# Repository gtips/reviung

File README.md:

# REVIUNG

## [REVIUNG41](https://github.com/gtips/reviung/tree/master/reviung41)  

The REVIUNG41 is 41-key column staggered keyboard.  

[Firmware](https://github.com/qmk/qmk_firmware/tree/master/keyboards/reviung/reviung41)  
[Build guide](https://reviung.com/build-guide/391/)  
  
<br>
<br>
  
## REVIUNG39 Mk-II, REVIUNG39 and REVIUNG39S  
The REVIUNG39 is 39-key column staggered keyboard.

Soldering is divided into through-hole mounting version and surface mounting (SMD) version so that the soldering difficulty can be selected.  

- REVIUNG39 Mk-II and REVIUNG39 is regular version (SMD)  
- REVIUNG39S is simple version (through-hole)  

[REVIUNG39 Mk-II ](https://github.com/gtips/reviung/tree/master/reviung39Mk-II)   

<br>

[REVIUNG39](https://github.com/gtips/reviung/tree/master/reviung39)  

<br>

[REVIUNG39 Build guide](https://reviung.com/build-guide/108/)  
[Firmware](https://github.com/qmk/qmk_firmware/tree/master/keyboards/reviung/reviung39)
  
<br>
<br>

## REVIUNG34  
The REVIUNG34 is 34-key (or33-key) column staggered keyboard.  
  
[REVIUNG34](https://github.com/gtips/reviung/tree/master/reviung34)  

<br>

[REVIUNG34 Build guide](https://reviung.com/build-guide/724/)  
[Firmware](https://github.com/qmk/qmk_firmware/tree/master/keyboards/reviung/reviung34)
  
<br>
<br>

## REVIUNG5  
The REVIUNG5 is 5-key (or 4-key + Rotary Encoder) macropad.  
  
[REVIUNG5](https://github.com/gtips/reviung/tree/master/reviung5)  

<br>

[REVIUNG5 Build guide](https://reviung.com/build-guide/)  
[Firmware](https://github.com/qmk/qmk_firmware/tree/master/keyboards/reviung/reviung5)
  
<br>
<br>
  
## REVIUNG34 SPLIT Mk-II and REVIUNG34 SPLIT  

The REVIUNG34 is 34-key split ortholinear keyboard.  
(REVIUNG34 SPLIT Mk-II is 34-key or 33-key)  
Use a LAN cable to connect the left and right keyboards.  
  
[REVIUNG34 Mk-II](https://github.com/gtips/reviung/tree/master/reviung34split_Mk-II)  

<br>
  
[REVIUNG34 SPLIT](https://github.com/gtips/reviung/tree/master/reviung34split)  

[Firmware](https://github.com/qmk/qmk_firmware/tree/master/keyboards/reviung/reviung34)  
[REVIUNG34 SPLIT Build guide](https://reviung.com/build-guide/278/)  

<br>
<br>

## [REVIUNG33](https://github.com/gtips/reviung/tree/master/reviung33)  

The REVIUNG33 is 33-key ortholinear keyboard.  

[Firmware](https://github.com/qmk/qmk_firmware/tree/master/keyboards/reviung/reviung33)  

<br>
<br>

## [REVIUNG53](https://github.com/gtips/reviung/tree/master/reviung53)  

The REVIUNG53 is 53-key keyboard.  

[Firmware](https://github.com/qmk/qmk_firmware/tree/master/keyboards/reviung/reviung53)  

<br>
<br>

## [REVIUNG61](https://github.com/gtips/reviung/tree/master/reviung61)  

Standard ANSI 60% keyboard. And compatible with MX and ALPS.  

[Firmware](https://github.com/qmk/qmk_firmware/tree/master/keyboards/reviung/reviung61)  

<br>
<br>

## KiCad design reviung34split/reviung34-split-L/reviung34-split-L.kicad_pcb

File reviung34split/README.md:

# REVIUNG34 SPLIT  

The REVIUNG34 SPLIT is 34-key split ortholinear keyboard.  
Use a LAN cable to connect the left and right keyboards.  

[Firmware](https://github.com/qmk/qmk_firmware/tree/master/keyboards/reviung/reviung34)  
[Build guide](https://reviung.com/build-guide/278/)  

#### Parts list  
1  PCB left  
1  PCB right  
1  left Top plate (PCB with switch mounting holes)  
1  right Top plate (PCB with switch mounting hole)  
2  Bottom plate (left and right common PCB)  
1  ProMicro protective plate (Comes with left top plate. Cut and use.)  
34 Diode (1N4148)  
34 PCB socket for switches  
1  Tact switch (reset button)  
2  Ethernet connector (DS1128-05-S8B8P)  
1  Stabilizer (2u)  
12 M2 spacer 7mm (metal spacer)  
24 M2 screw 5mm  
8  Rubber feet for bottom plate  
<br/>
1  ProMicro  
34 Key switch (MX compatible)  
33 Keycap (1U, MX compatible)  
1  Keycap (2U, MX compatible)  
1  MicroUSB cable  
1  Ethernet cable (Use a cable shorter than 1m)

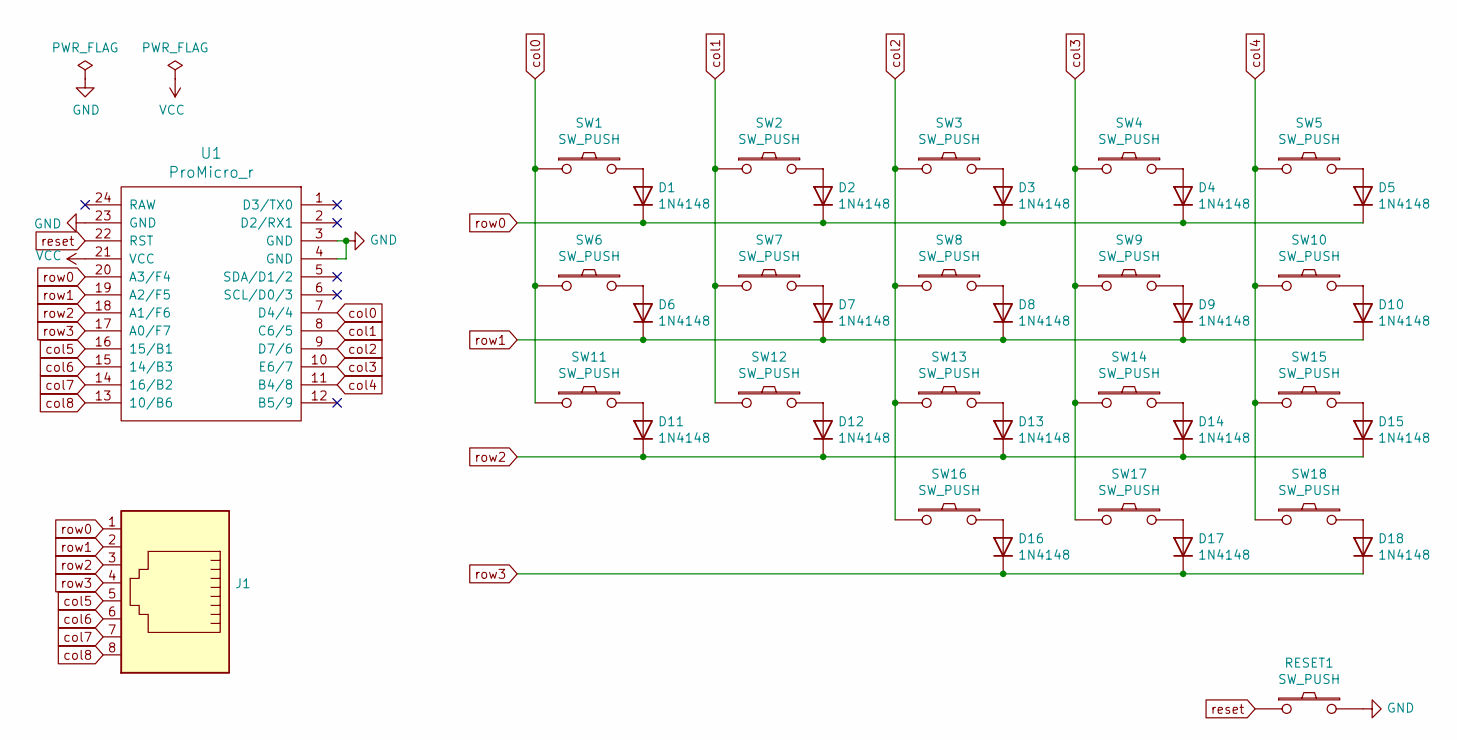
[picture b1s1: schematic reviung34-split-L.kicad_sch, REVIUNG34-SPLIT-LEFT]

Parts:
D1, D2, D3, D4, D5, D6, D7, D8, D9, D10, D11, D12, D13, D14, D15, D16, D17, D18: 1N4148; D_DO-35_SOD27_P7.62mm_Horizontal
J1: (no value)
RESET1: SW_PUSH; ResetSW_1side
SW1, SW2, SW3, SW4, SW5, SW6, SW7, SW8, SW9, SW10, SW11, SW12, SW13, SW14, SW15, SW16, SW17, SW18: SW_PUSH; MXOnly-1U-Hotswap
U1: ProMicro_r; ProMicro

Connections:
GND: RESET1.2, U1.3 (GND), U1.4 (GND), U1.23 (GND)
unnamed: D1.2 (A), SW1.2
unnamed: D2.2 (A), SW2.2
unnamed: D3.2 (A), SW3.2
unnamed: D4.2 (A), SW4.2
unnamed: D5.2 (A), SW5.2
unnamed: D6.2 (A), SW6.2
unnamed: D7.2 (A), SW7.2
unnamed: D8.2 (A), SW8.2
unnamed: D9.2 (A), SW9.2
unnamed: D10.2 (A), SW10.2
unnamed: D11.2 (A), SW11.2
unnamed: D12.2 (A), SW12.2
unnamed: D13.2 (A), SW13.2
unnamed: D14.2 (A), SW14.2
unnamed: D15.2 (A), SW15.2
unnamed: D16.2 (A), SW16.2
unnamed: D17.2 (A), SW17.2
unnamed: D18.2 (A), SW18.2
VCC: U1.21 (VCC)
col0: SW1.1, SW6.1, SW11.1, U1.7 (D4/4)
col1: SW2.1, SW7.1, SW12.1, U1.8 (C6/5)
col2: SW3.1, SW8.1, SW13.1, SW16.1, U1.9 (D7/6)
col3: SW4.1, SW9.1, SW14.1, SW17.1, U1.10 (E6/7)
col4: SW5.1, SW10.1, SW15.1, SW18.1, U1.11 (B4/8)
col5: J1.5, U1.16 (15/B1)
col6: J1.6, U1.15 (14/B3)
col7: J1.7, U1.14 (16/B2)
col8: J1.8, U1.13 (10/B6)
reset: RESET1.1, U1.22 (RST)
row0: D1.1 (K), D2.1 (K), D3.1 (K), D4.1 (K), D5.1 (K), J1.1, U1.20 (A3/F4)
row1: D6.1 (K), D7.1 (K), D8.1 (K), D9.1 (K), D10.1 (K), J1.2, U1.19 (A2/F5)
row2: D11.1 (K), D12.1 (K), D13.1 (K), D14.1 (K), D15.1 (K), J1.3, U1.18 (A1/F6)
row3: D16.1 (K), D17.1 (K), D18.1 (K), J1.4, U1.17 (A0/F7)

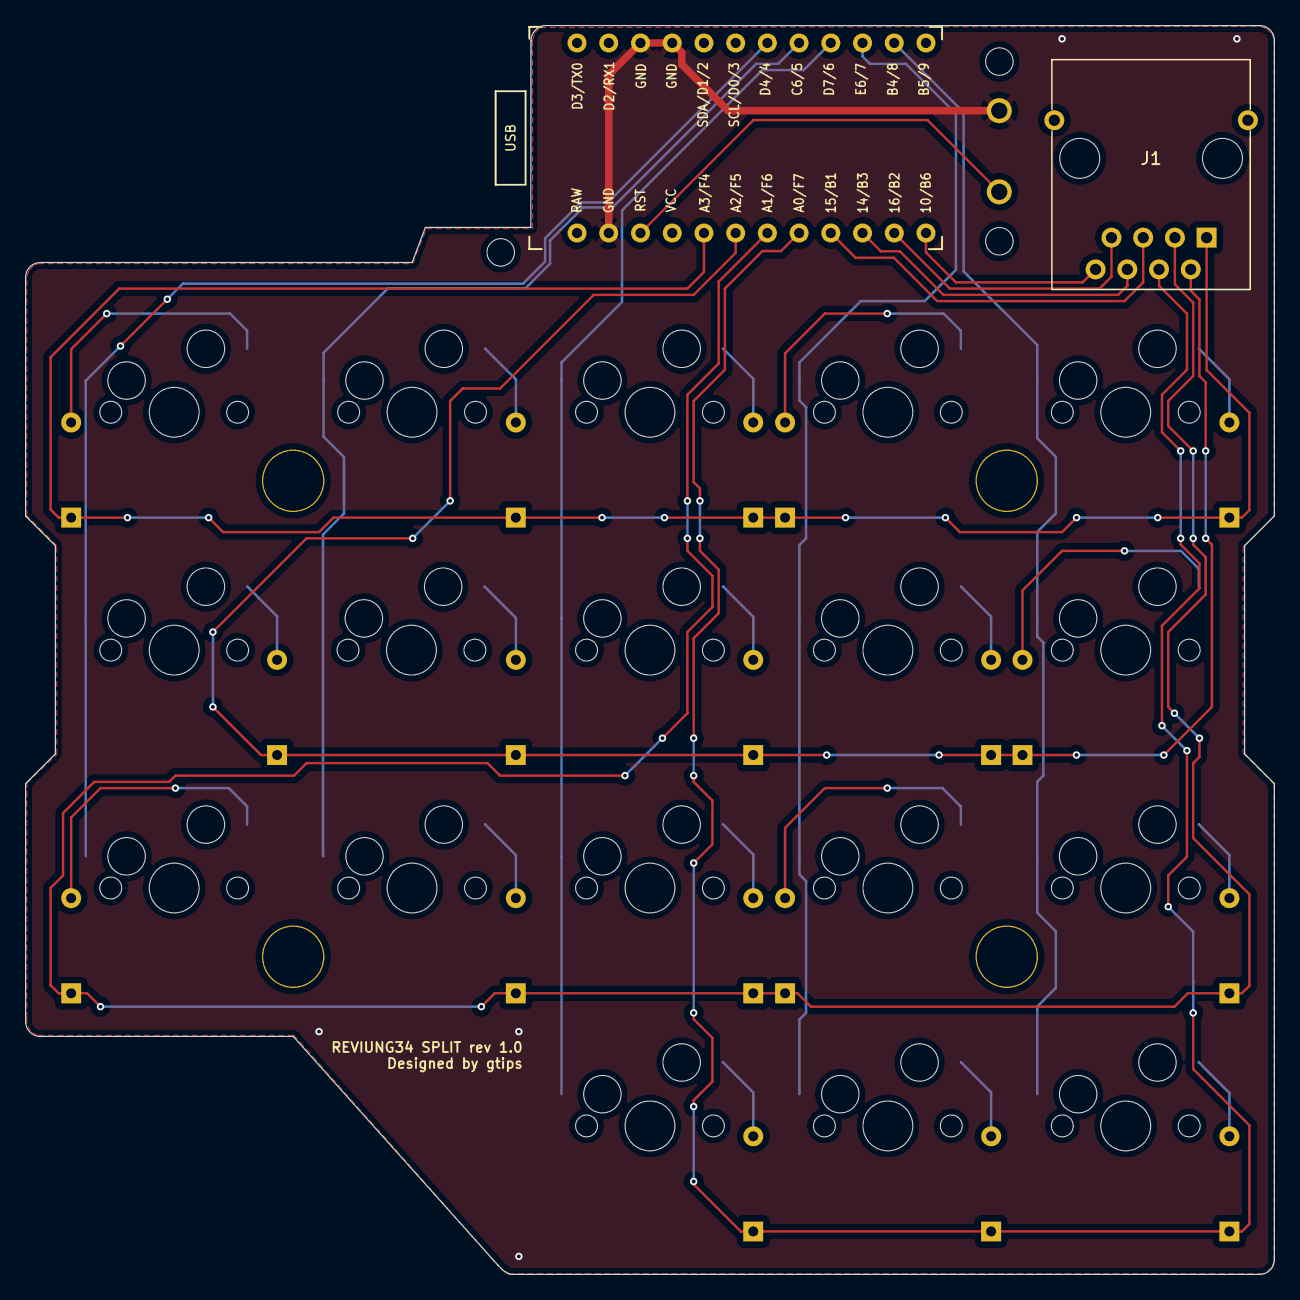
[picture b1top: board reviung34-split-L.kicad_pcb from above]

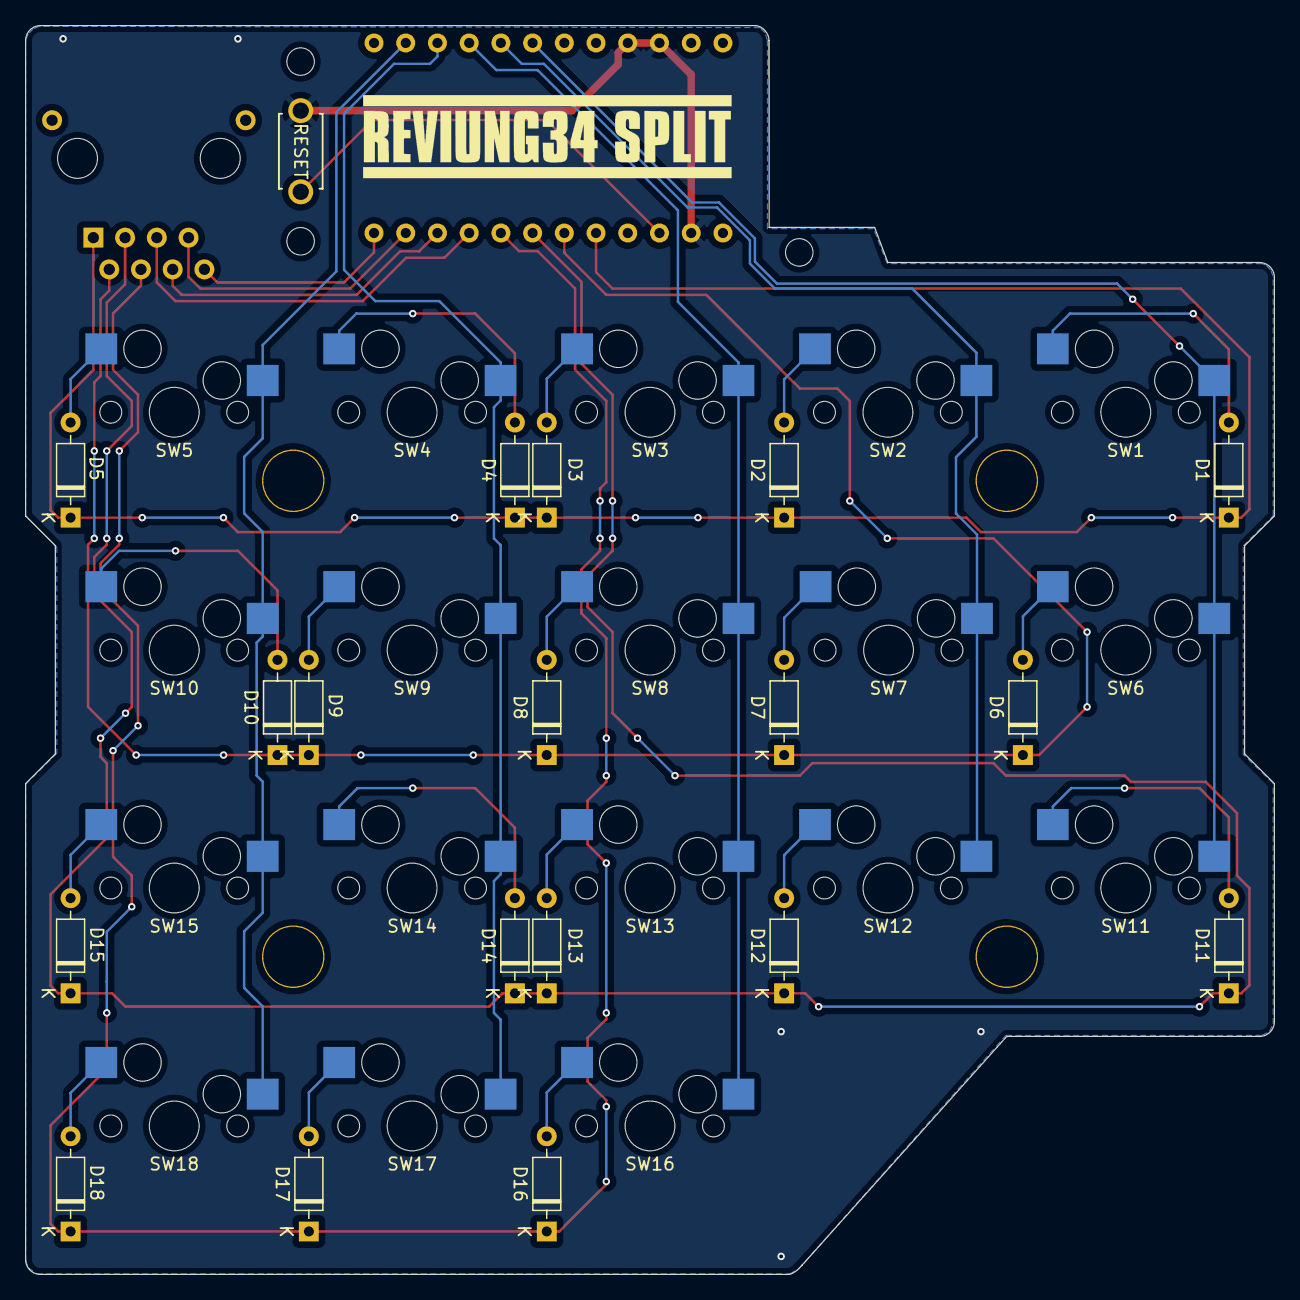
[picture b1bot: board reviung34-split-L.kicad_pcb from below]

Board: 2 copper layers, 100.0 x 100.0 mm, 46 parts (19 on the bottom side), 33 nets.

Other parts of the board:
H1: H1; HOLE
H2: H2; HOLE
H3: H3; HOLE
H4: H4; HOLE
H5, H6, H7: MountingHole_2.2mm_M2

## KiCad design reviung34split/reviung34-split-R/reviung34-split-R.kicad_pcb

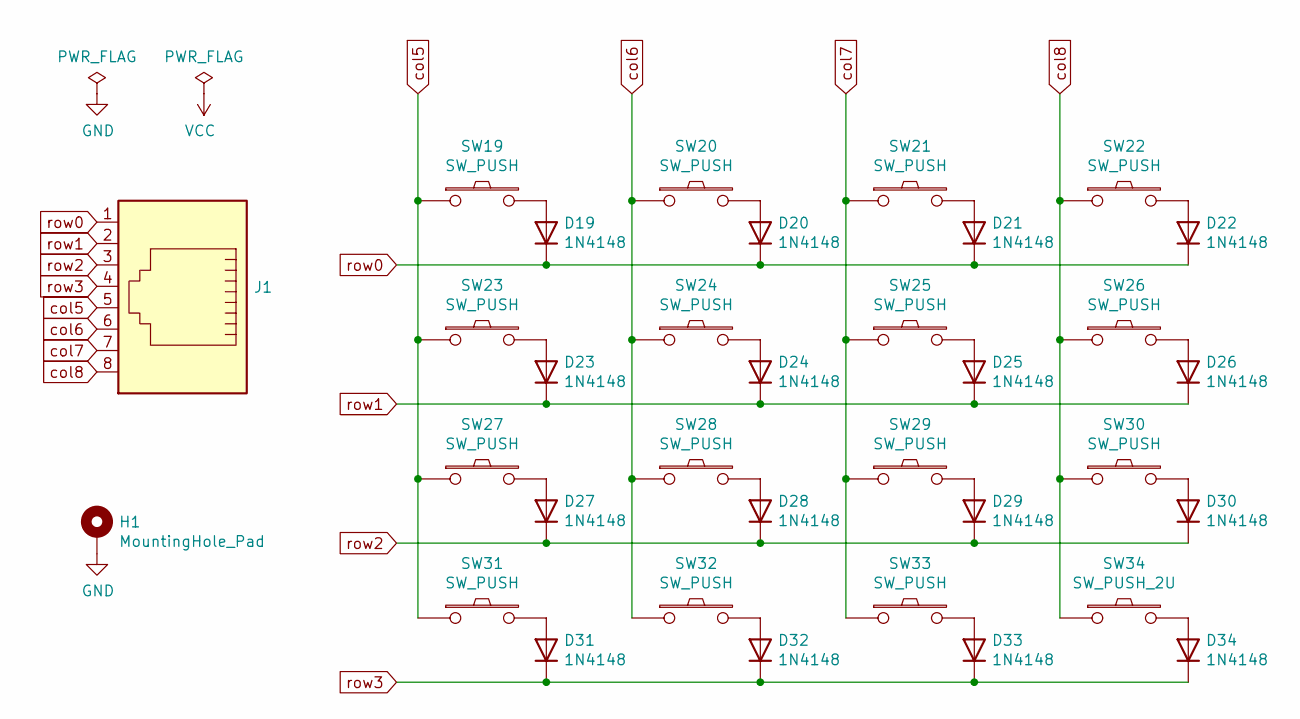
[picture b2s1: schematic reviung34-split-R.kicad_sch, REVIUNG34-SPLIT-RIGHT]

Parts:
D19, D20, D21, D22, D23, D24, D25, D26, D27, D28, D29, D30, D31, D32, D33, D34: 1N4148; D_DO-35_SOD27_P7.62mm_Horizontal
H1: MountingHole_Pad; MountingHole_4.3mm_M4_ISO14580_Pad
J1: (no value)
SW19, SW20, SW21, SW22, SW23, SW24, SW25, SW26, SW27, SW28, SW29, SW30, SW31, SW32, SW33: SW_PUSH; MXOnly-1U-Hotswap
SW34: SW_PUSH_2U; MXOnly-2U-Hotswap-ReversedStabilizers

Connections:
GND: H1.1, J1.SH
unnamed: D19.2 (A), SW19.2
unnamed: D20.2 (A), SW20.2
unnamed: D21.2 (A), SW21.2
unnamed: D22.2 (A), SW22.2
unnamed: D23.2 (A), SW23.2
unnamed: D24.2 (A), SW24.2
unnamed: D25.2 (A), SW25.2
unnamed: D26.2 (A), SW26.2
unnamed: D27.2 (A), SW27.2
unnamed: D28.2 (A), SW28.2
unnamed: D29.2 (A), SW29.2
unnamed: D30.2 (A), SW30.2
unnamed: D31.2 (A), SW31.2
unnamed: D32.2 (A), SW32.2
unnamed: D33.2 (A), SW33.2
unnamed: D34.2 (A), SW34.2
col5: J1.5, SW19.1, SW23.1, SW27.1, SW31.1
col6: J1.6, SW20.1, SW24.1, SW28.1, SW32.1
col7: J1.7, SW21.1, SW25.1, SW29.1, SW33.1
col8: J1.8, SW22.1, SW26.1, SW30.1, SW34.1
row0: D19.1 (K), D20.1 (K), D21.1 (K), D22.1 (K), J1.1
row1: D23.1 (K), D24.1 (K), D25.1 (K), D26.1 (K), J1.2
row2: D27.1 (K), D28.1 (K), D29.1 (K), D30.1 (K), J1.3
row3: D31.1 (K), D32.1 (K), D33.1 (K), D34.1 (K), J1.4

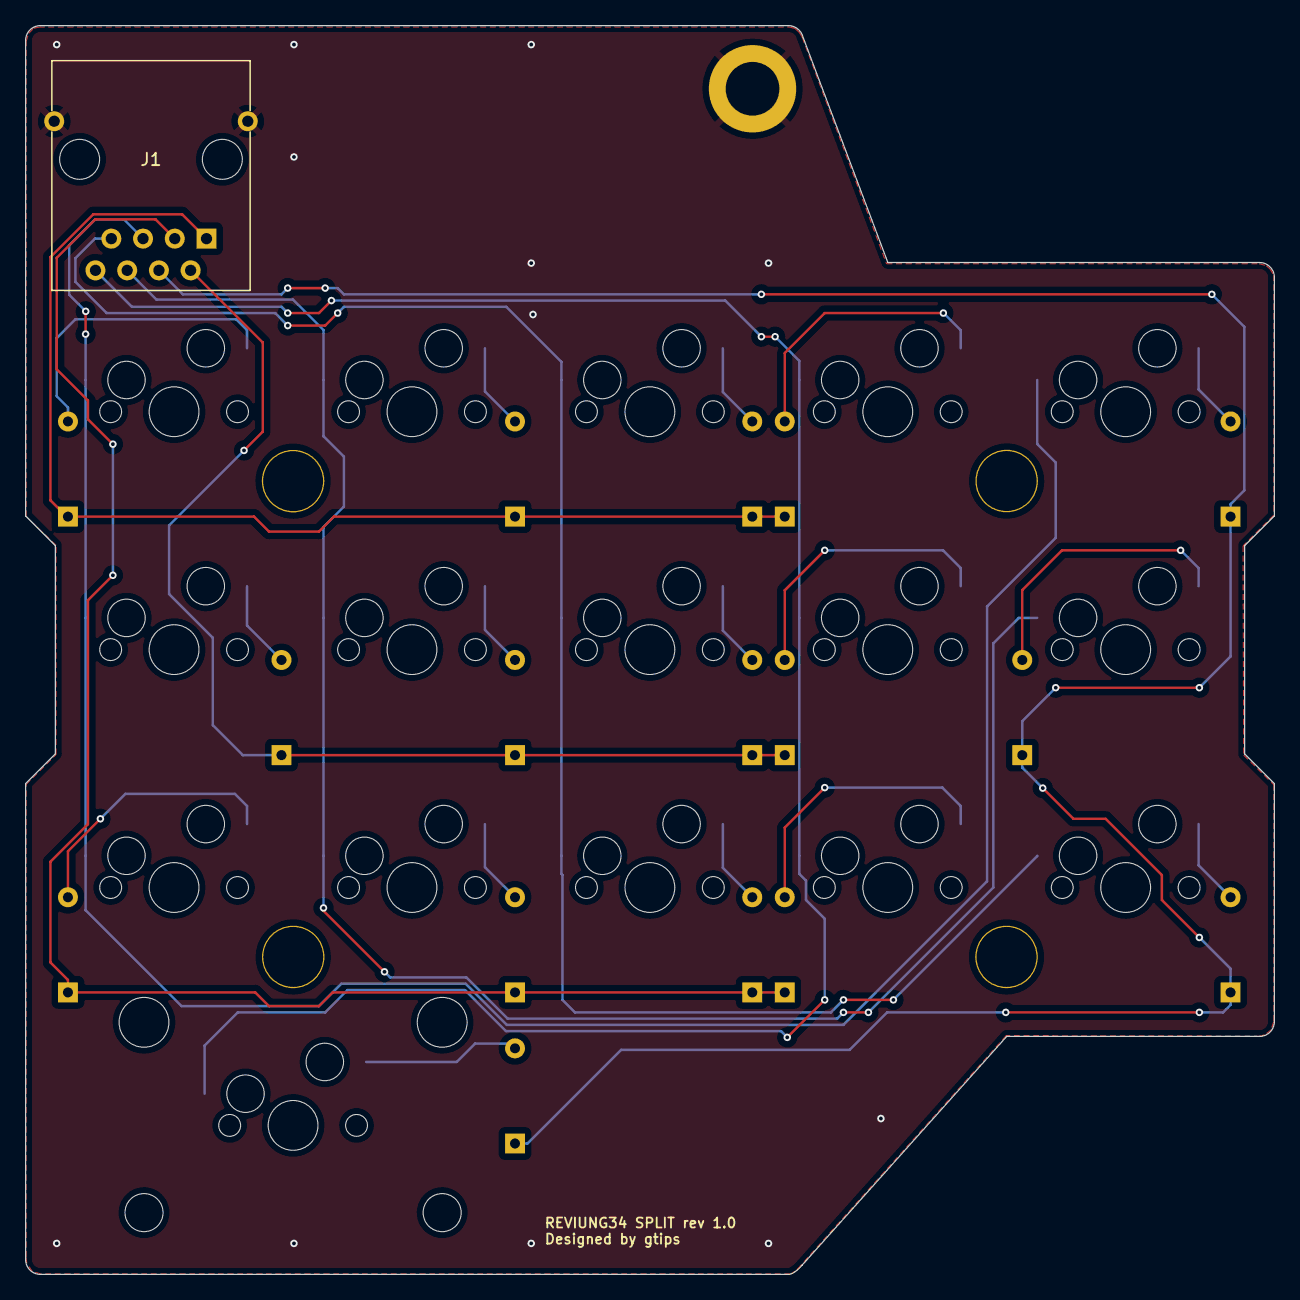
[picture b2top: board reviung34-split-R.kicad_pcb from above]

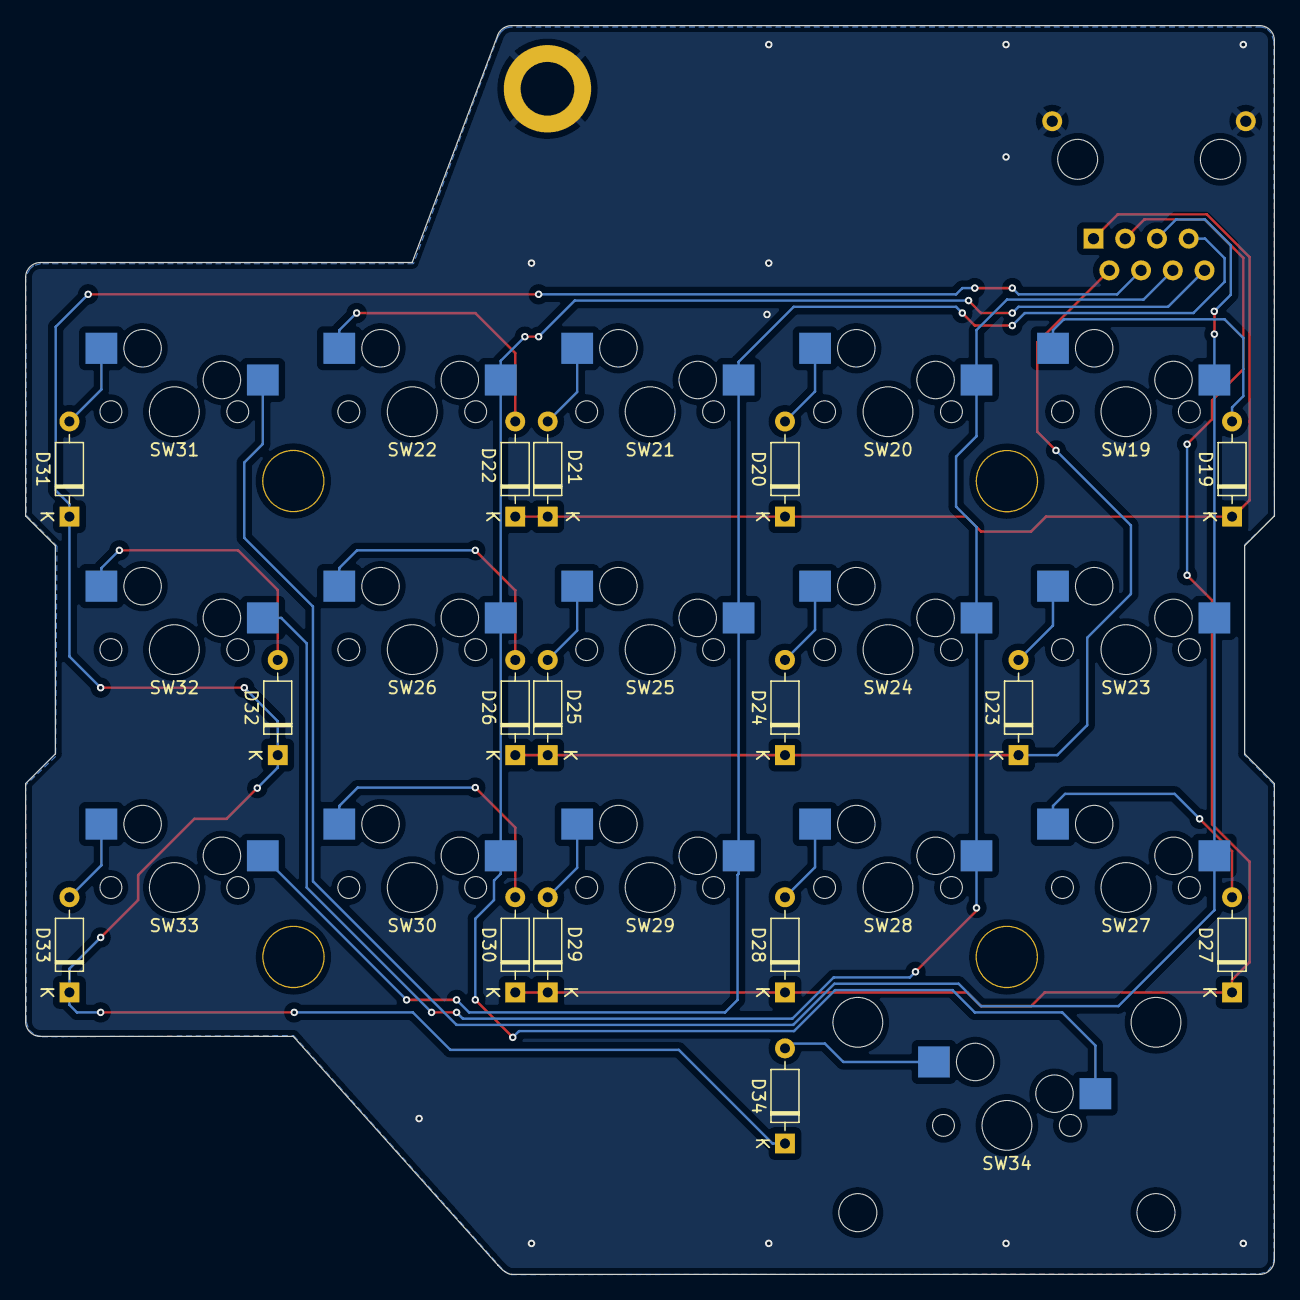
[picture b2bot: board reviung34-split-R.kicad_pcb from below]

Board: 2 copper layers, 100.0 x 100.0 mm, 38 parts (16 on the bottom side), 25 nets.

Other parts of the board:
H2: H2; HOLE
H3: H3; HOLE
H4: H4; HOLE
H5: H5; HOLE

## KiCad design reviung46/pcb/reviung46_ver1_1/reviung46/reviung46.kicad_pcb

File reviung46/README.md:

# REVIUNG46  

The REVIUNG46 is 42-46 key keyboard.

[Build guide](https://reviung.com/build-guide/)

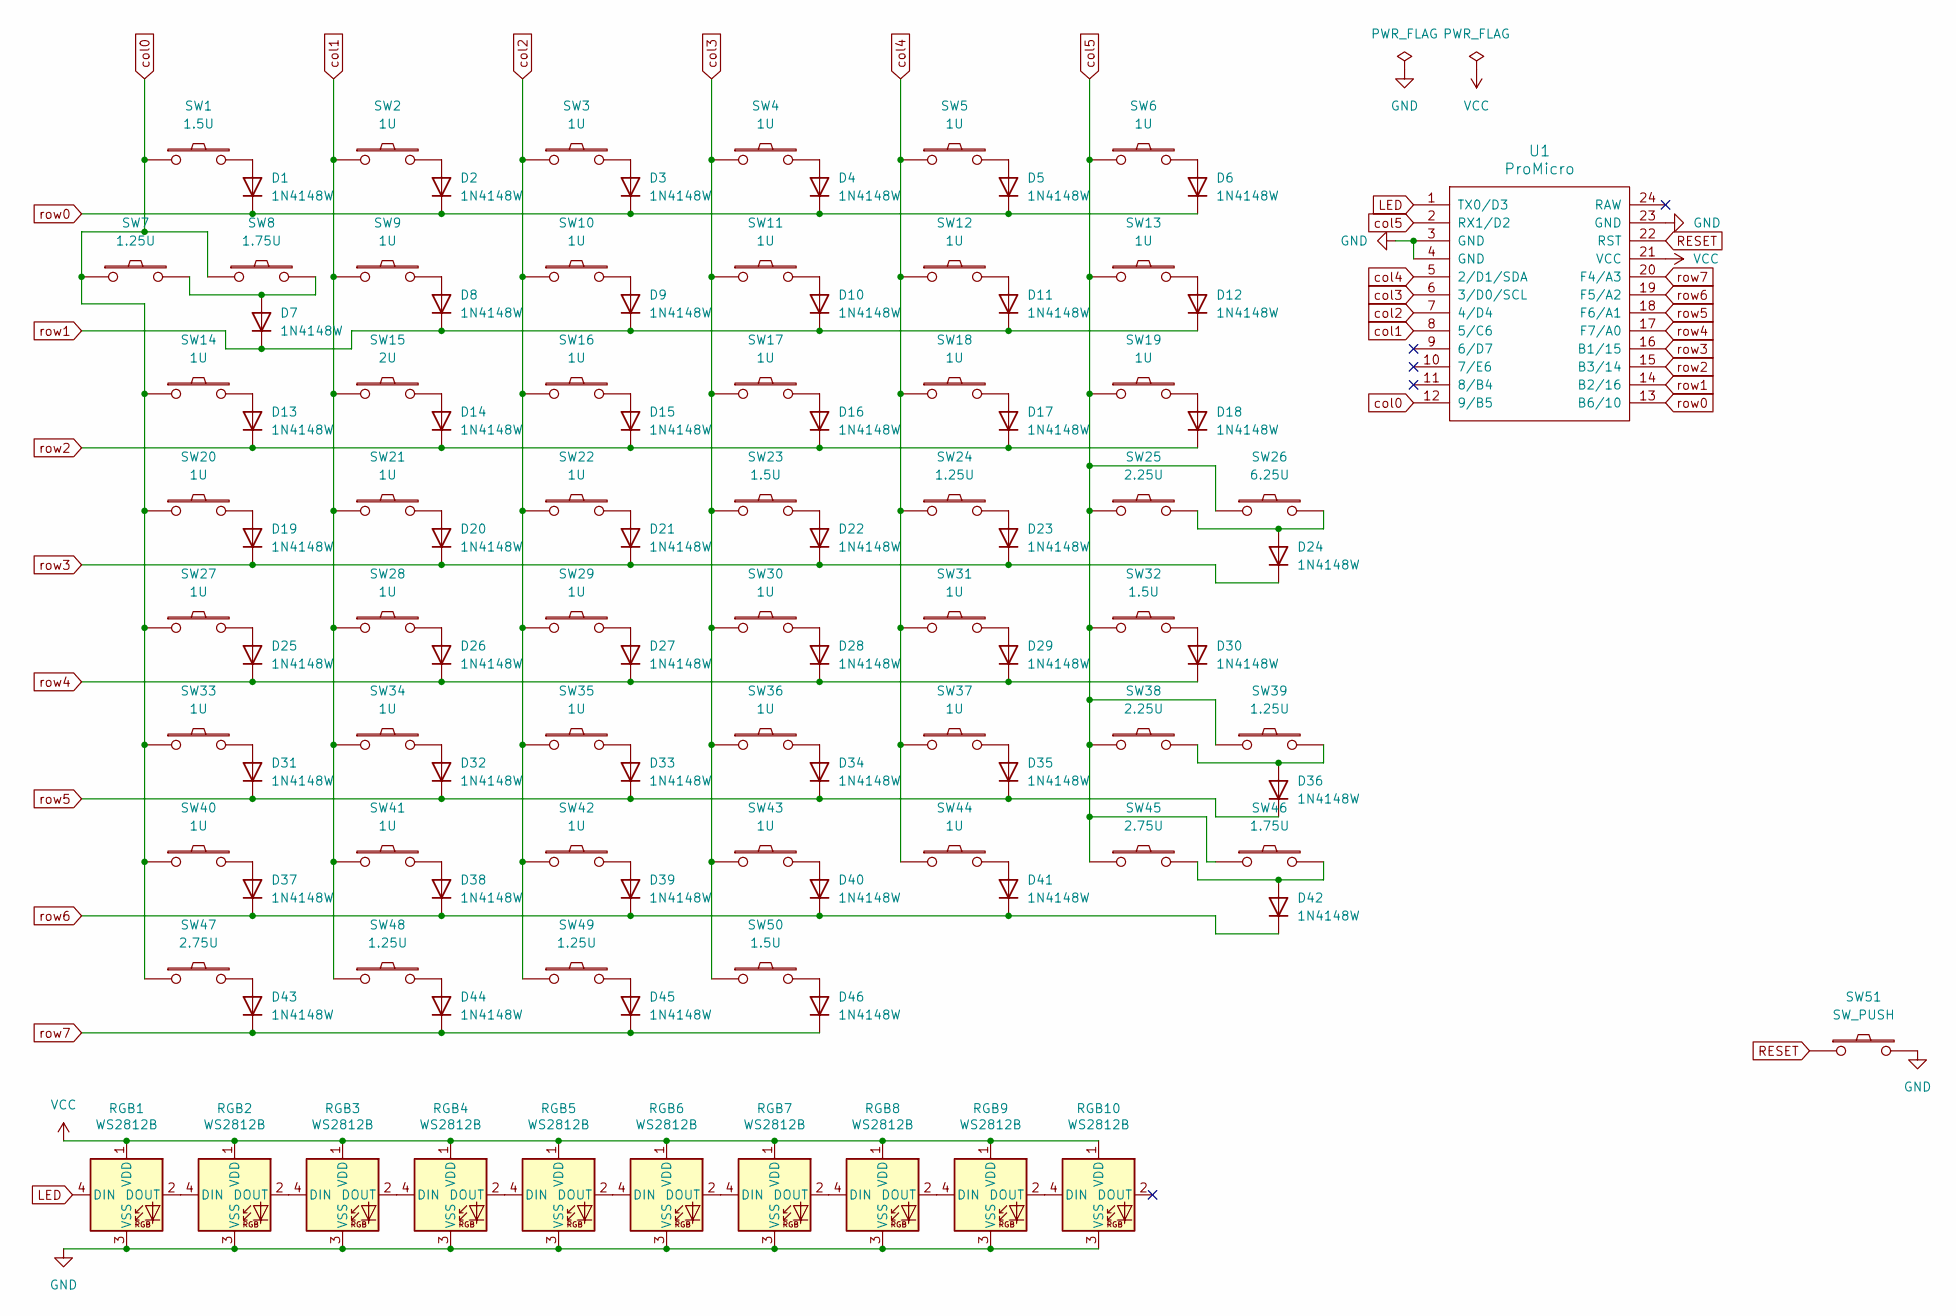
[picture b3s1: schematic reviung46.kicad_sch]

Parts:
D1, D2, D3, D4, D5, D6, D7, D8, D9, D10, D11, D12, D13, D14, D15, D16, D17, D18, D19, D20, D21, D22, D23, D24, D25, D26, D27, D28, D29, D30, D31, D32, D33, D34, D35, D36, D37, D38, D39, D40, D41, D42, D43, D44, D45, D46: 1N4148W; D3_SMD_1side
RGB1, RGB2, RGB3, RGB4, RGB5, RGB6, RGB7, RGB8, RGB9, RGB10: WS2812B; LED_WS2812B_PLCC4_5.0x5.0mm_P3.2mm_BigFoot
SW1, SW23, SW32, SW50: 1.5U; MXOnly-1.5U-Hotswap
SW2, SW3, SW4, SW5, SW6, SW9, SW10, SW11, SW12, SW13, SW14, SW16, SW17, SW18, SW19, SW20, SW21, SW22, SW27, SW28, SW29, SW30, SW31, SW33, SW34, SW35, SW36, SW37, SW40, SW41, SW42, SW43, SW44: 1U; MXOnly-1U-Hotswap
SW7, SW24, SW39, SW48, SW49: 1.25U; MXOnly-1.25U-Hotswap
SW8, SW46: 1.75U; MXOnly-1.75U-Hotswap
SW15: 2U; MXOnly-2U-Hotswap-ReversedStabilizers
SW25: 2.25U; MXOnly-2.25U-Hotswap
SW26: 6.25U; MXOnly-6.25U-Hotswap-ReversedStabilizers
SW38: 2.25U; MXOnly-2.25U-Hotswap-ReversedStabilizers
SW45, SW47: 2.75U; MXOnly-2.75U-Hotswap-ReversedStabilizers
SW51: SW_PUSH; ResetSW_1side
U1: ProMicro; ProMicroExtentionBard

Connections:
GND: RGB1.3 (VSS), RGB2.3 (VSS), RGB3.3 (VSS), RGB4.3 (VSS), RGB5.3 (VSS), RGB6.3 (VSS), RGB7.3 (VSS), RGB8.3 (VSS), RGB9.3 (VSS), RGB10.3 (VSS), SW51.2, U1.3 (GND), U1.4 (GND), U1.23 (GND)
LED: RGB1.4 (DIN), U1.1 (TX0/D3)
unnamed: D1.2 (A), SW1.2
unnamed: D2.2 (A), SW2.2
unnamed: D3.2 (A), SW3.2
unnamed: D4.2 (A), SW4.2
unnamed: D5.2 (A), SW5.2
unnamed: D6.2 (A), SW6.2
unnamed: D7.2 (A), SW7.2, SW8.2
unnamed: D8.2 (A), SW9.2
unnamed: D9.2 (A), SW10.2
unnamed: D10.2 (A), SW11.2
unnamed: D11.2 (A), SW12.2
unnamed: D12.2 (A), SW13.2
unnamed: D13.2 (A), SW14.2
unnamed: D14.2 (A), SW15.2
unnamed: D15.2 (A), SW16.2
unnamed: D16.2 (A), SW17.2
unnamed: D17.2 (A), SW18.2
unnamed: D18.2 (A), SW19.2
unnamed: D19.2 (A), SW20.2
unnamed: D20.2 (A), SW21.2
unnamed: D21.2 (A), SW22.2
unnamed: D22.2 (A), SW23.2
unnamed: D23.2 (A), SW24.2
unnamed: D24.2 (A), SW25.2, SW26.2
unnamed: D25.2 (A), SW27.2
unnamed: D26.2 (A), SW28.2
unnamed: D27.2 (A), SW29.2
unnamed: D28.2 (A), SW30.2
unnamed: D29.2 (A), SW31.2
unnamed: D30.2 (A), SW32.2
unnamed: D31.2 (A), SW33.2
unnamed: D32.2 (A), SW34.2
unnamed: D33.2 (A), SW35.2
unnamed: D34.2 (A), SW36.2
unnamed: D35.2 (A), SW37.2
unnamed: D36.2 (A), SW38.2, SW39.2
unnamed: D37.2 (A), SW40.2
unnamed: D38.2 (A), SW41.2
unnamed: D39.2 (A), SW42.2
unnamed: D40.2 (A), SW43.2
unnamed: D41.2 (A), SW44.2
unnamed: D42.2 (A), SW45.2, SW46.2
unnamed: D43.2 (A), SW47.2
unnamed: D44.2 (A), SW48.2
unnamed: D45.2 (A), SW49.2
unnamed: D46.2 (A), SW50.2
unnamed: RGB1.2 (DOUT), RGB2.4 (DIN)
unnamed: RGB2.2 (DOUT), RGB3.4 (DIN)
unnamed: RGB3.2 (DOUT), RGB4.4 (DIN)
unnamed: RGB4.2 (DOUT), RGB5.4 (DIN)
unnamed: RGB5.2 (DOUT), RGB6.4 (DIN)
unnamed: RGB6.2 (DOUT), RGB7.4 (DIN)
unnamed: RGB7.2 (DOUT), RGB8.4 (DIN)
unnamed: RGB8.2 (DOUT), RGB9.4 (DIN)
unnamed: RGB9.2 (DOUT), RGB10.4 (DIN)
RESET: SW51.1, U1.22 (RST)
VCC: RGB1.1 (VDD), RGB2.1 (VDD), RGB3.1 (VDD), RGB4.1 (VDD), RGB5.1 (VDD), RGB6.1 (VDD), RGB7.1 (VDD), RGB8.1 (VDD), RGB9.1 (VDD), RGB10.1 (VDD), U1.21 (VCC)
col0: SW1.1, SW7.1, SW8.1, SW14.1, SW20.1, SW27.1, SW33.1, SW40.1, SW47.1, U1.12 (9/B5)
col1: SW2.1, SW9.1, SW15.1, SW21.1, SW28.1, SW34.1, SW41.1, SW48.1, U1.8 (5/C6)
col2: SW3.1, SW10.1, SW16.1, SW22.1, SW29.1, SW35.1, SW42.1, SW49.1, U1.7 (4/D4)
col3: SW4.1, SW11.1, SW17.1, SW23.1, SW30.1, SW36.1, SW43.1, SW50.1, U1.6 (3/D0/SCL)
col4: SW5.1, SW12.1, SW18.1, SW24.1, SW31.1, SW37.1, SW44.1, U1.5 (2/D1/SDA)
col5: SW6.1, SW13.1, SW19.1, SW25.1, SW26.1, SW32.1, SW38.1, SW39.1, SW45.1, SW46.1, U1.2 (RX1/D2)
row0: D1.1 (K), D2.1 (K), D3.1 (K), D4.1 (K), D5.1 (K), D6.1 (K), U1.13 (B6/10)
row1: D7.1 (K), D8.1 (K), D9.1 (K), D10.1 (K), D11.1 (K), D12.1 (K), U1.14 (B2/16)
row2: D13.1 (K), D14.1 (K), D15.1 (K), D16.1 (K), D17.1 (K), D18.1 (K), U1.15 (B3/14)
row3: D19.1 (K), D20.1 (K), D21.1 (K), D22.1 (K), D23.1 (K), D24.1 (K), U1.16 (B1/15)
row4: D25.1 (K), D26.1 (K), D27.1 (K), D28.1 (K), D29.1 (K), D30.1 (K), U1.17 (F7/A0)
row5: D31.1 (K), D32.1 (K), D33.1 (K), D34.1 (K), D35.1 (K), D36.1 (K), U1.18 (F6/A1)
row6: D37.1 (K), D38.1 (K), D39.1 (K), D40.1 (K), D41.1 (K), D42.1 (K), U1.19 (F5/A2)
row7: D43.1 (K), D44.1 (K), D45.1 (K), D46.1 (K), U1.20 (F4/A3)

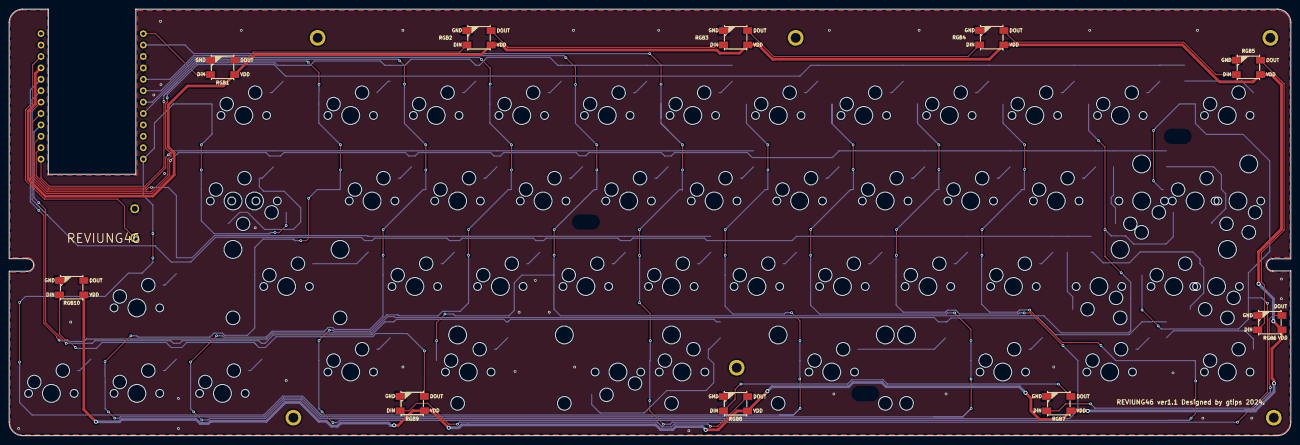
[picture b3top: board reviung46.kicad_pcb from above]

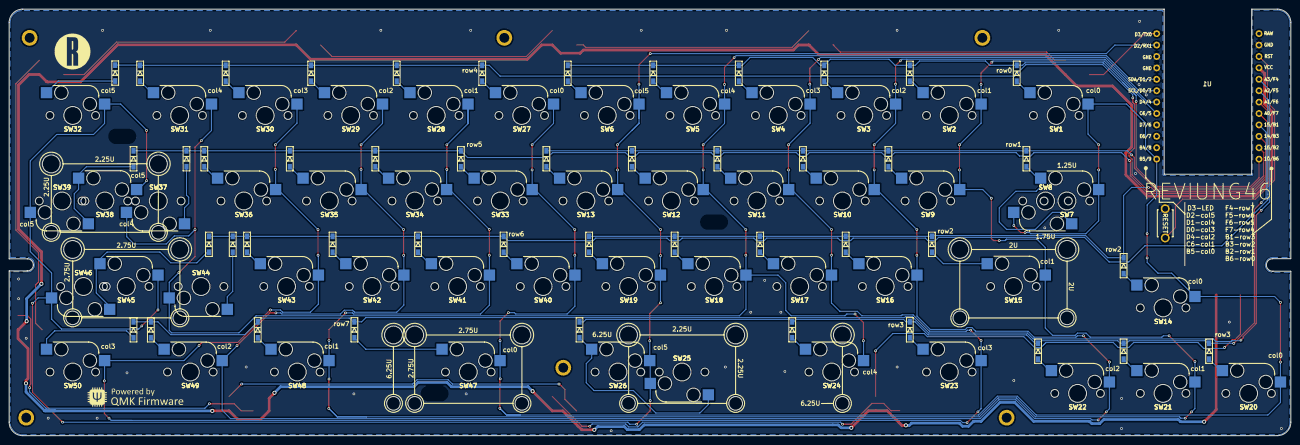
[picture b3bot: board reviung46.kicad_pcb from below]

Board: 2 copper layers, 285.5 x 95.0 mm, 112 parts (47 on the bottom side), 73 nets.

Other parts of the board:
Ref**: Val**; MountingHole_2.2mm_M2_ISO7380_Pad
Ref**#2, Ref**#3, Ref**#4: Val**; MountingHole_2.2mm_M2_ISO7380_Pad
